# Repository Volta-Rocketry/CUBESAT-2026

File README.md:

# CUBESAT-2026
Repo for the CUBESAT - 2026

/ IMAGE OR VIDEO

## Description

Here goes the project description

## Features
Here goes the features and capabilities

## Requirements and Software
Here goes the requirements for developers to run the code

## Usage
Here goes a little guide or referral to usage manual

### IMPORTANT
Here goes important notes

## Authors and Acknowledgments
Here goes the authors and acknowledgments

## License
Here goes the license information

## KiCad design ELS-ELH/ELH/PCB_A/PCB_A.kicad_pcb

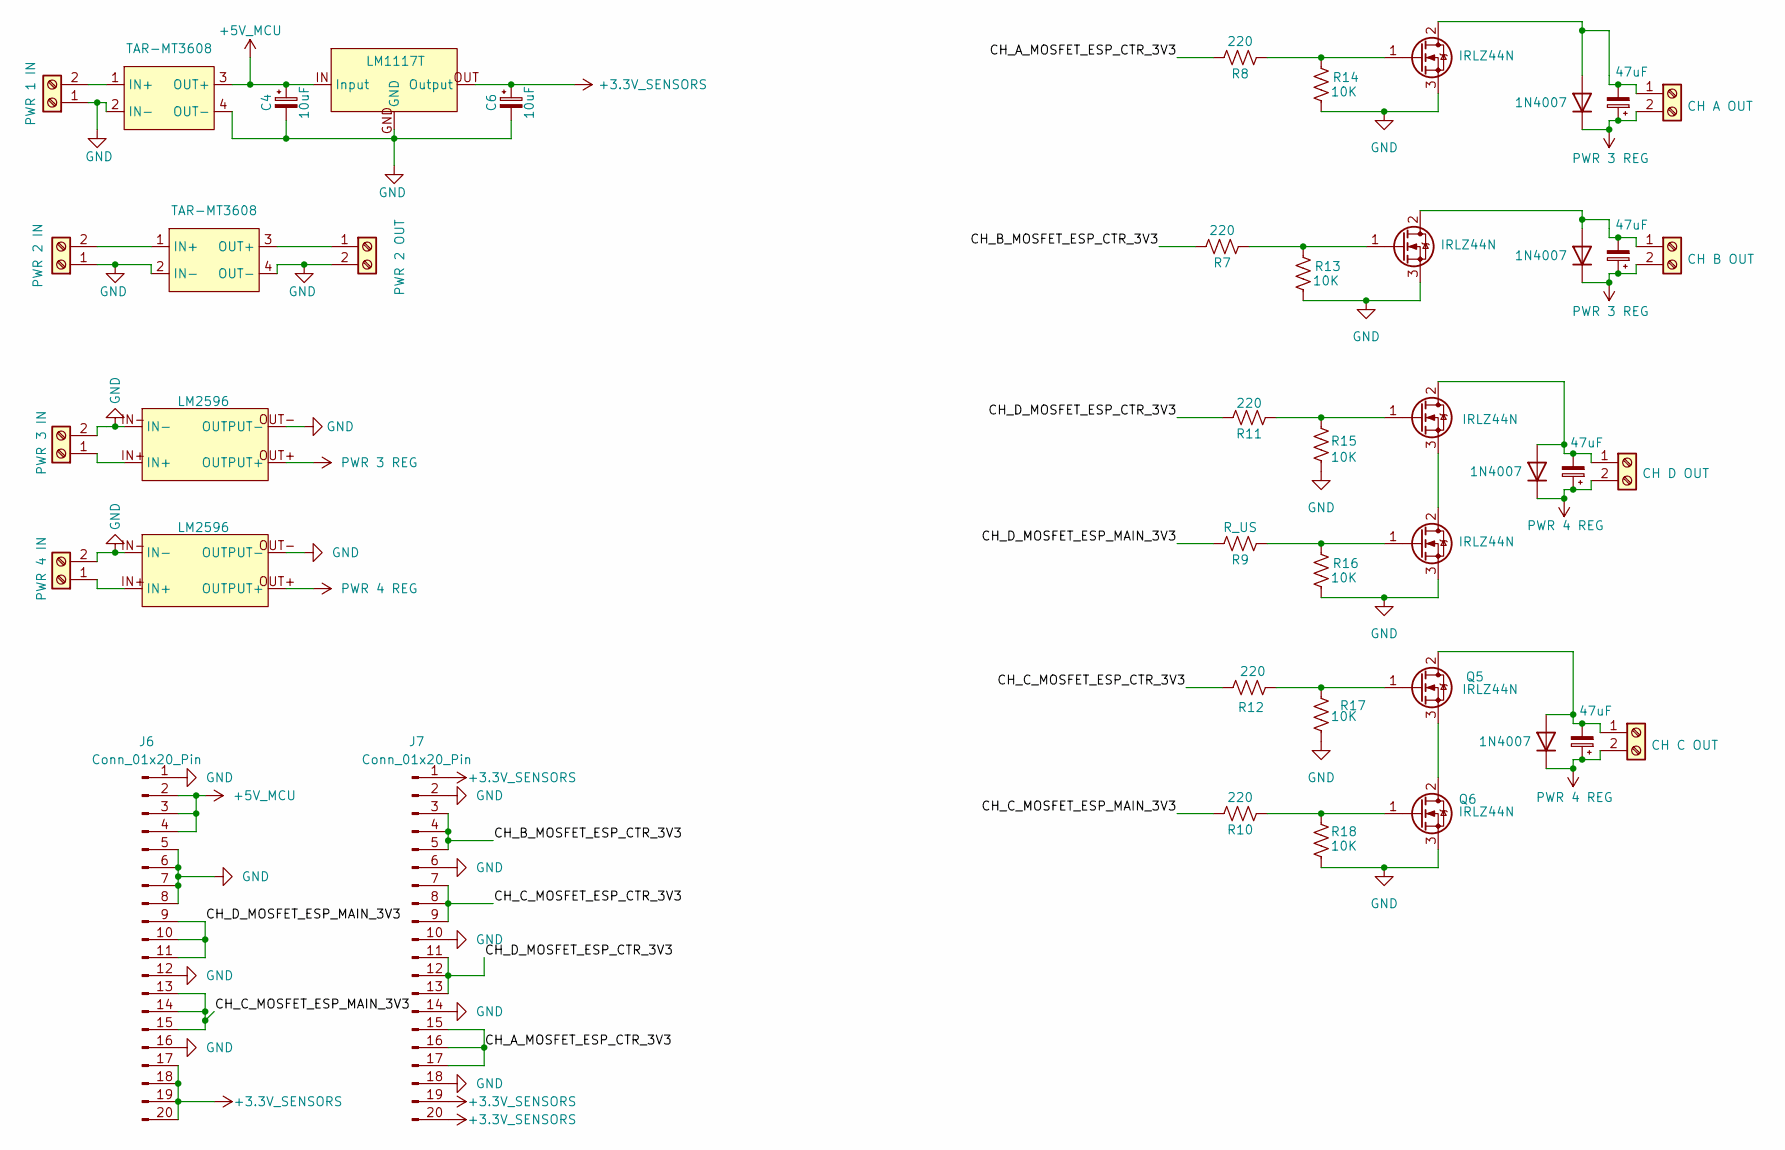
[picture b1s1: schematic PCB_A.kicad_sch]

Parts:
BOOST1, BOOST2: TAR-MT3608
C4, C6: 10uF; CP_Radial_D5.0mm_P2.00mm
C7, C8, C9, C10: 47uF; CP_Radial_D6.3mm_P2.50mm
D2, D3, D4, D5: 1N4007; D_DO-41_SOD81_P10.16mm_Horizontal
J1: PWR 1 IN; Bornera 2P
J2: PWR 2 IN; Bornera 2P
J3: PWR 3 IN; Bornera 2P
J4: PWR 4 IN; Bornera 2P
J5: PWR 2 OUT; Bornera 2P
J6, J7: Conn_01x20_Pin; PinHeader_1x20_P2.54mm_Vertical
J9: CH D OUT; Bornera 2P
J10: CH C OUT; Bornera 2P
J11: CH A OUT; Bornera 2P
J12: CH B OUT; Bornera 2P
Q1, Q2, Q3, Q4, Q5, Q6: IRLZ44N; TO-220-3_Vertical
R7, R8, R10, R11, R12: 220; R_Axial_DIN0207_L6.3mm_D2.5mm_P7.62mm_Horizontal
R9: R_US; R_Axial_DIN0207_L6.3mm_D2.5mm_P7.62mm_Horizontal
R13, R14, R15, R16, R17, R18: 10K; R_Axial_DIN0207_L6.3mm_D2.5mm_P7.62mm_Horizontal
Regulator1, Regulator2: LM2596
Regulator3: LM1117T

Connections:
+3.3V_SENSORS: C6.1, J6.17, J6.18, J6.19, J6.20, J7.1, J7.19, J7.20, Regulator3.OUT (Output)
+5V_MCU: BOOST1.3 (OUT+), C4.1, J6.2, J6.3, J6.4, Regulator3.IN (Input)
/CH_A_MOSFET_ESP_CTR_3V3: J7.15, J7.16, J7.17, R8.1
/CH_B_MOSFET_ESP_CTR_3V3: J7.3, J7.4, J7.5, R7.1
/CH_C_MOSFET_ESP_CTR_3V3: J7.7, J7.8, J7.9, R12.1
/CH_C_MOSFET_ESP_MAIN_3V3: J6.13, J6.14, J6.15, R10.1
/CH_D_MOSFET_ESP_CTR_3V3: J7.11, J7.12, J7.13, R11.1
/CH_D_MOSFET_ESP_MAIN_3V3: J6.9, J6.10, J6.11, R9.1
GND: BOOST1.2 (IN-), BOOST1.4 (OUT-), BOOST2.2 (IN-), BOOST2.4 (OUT-), C4.2, C6.2, J1.1, J2.1, J3.2, J4.2, J5.2, J6.1, J6.5, J6.6, J6.7, J6.8, J6.12, J6.16, J7.2, J7.6, J7.10, J7.14, J7.18, Q1.3 (S), Q2.3 (S), Q4.3 (S), Q6.3 (S), R13.2, R14.2, R15.2, R16.2, R17.2, R18.2, Regulator1.IN-, Regulator1.OUT- (OUTPUT-), Regulator2.IN-, Regulator2.OUT- (OUTPUT-), Regulator3.GND
unnamed: BOOST1.1 (IN+), J1.2
unnamed: BOOST2.1 (IN+), J2.2
unnamed: BOOST2.3 (OUT+), J5.1
unnamed: C7.2, D2.2 (A), J9.1, Q3.2 (D)
unnamed: C8.2, D3.2 (A), J10.1, Q5.2 (D)
unnamed: C9.2, D4.2 (A), J11.1, Q2.2 (D)
unnamed: C10.2, D5.2 (A), J12.1, Q1.2 (D)
unnamed: J3.1, Regulator1.IN+
unnamed: J4.1, Regulator2.IN+
unnamed: Q1.1 (G), R7.2, R13.1
unnamed: Q2.1 (G), R8.2, R14.1
unnamed: Q3.1 (G), R11.2, R15.1
unnamed: Q3.3 (S), Q4.2 (D)
unnamed: Q4.1 (G), R9.2, R16.1
unnamed: Q5.1 (G), R12.2, R17.1
unnamed: Q5.3 (S), Q6.2 (D)
unnamed: Q6.1 (G), R10.2, R18.1
PWR 3 REG: C9.1, C10.1, D4.1 (K), D5.1 (K), J11.2, J12.2, Regulator1.OUT+ (OUTPUT+)
PWR 4 REG: C7.1, C8.1, D2.1 (K), D3.1 (K), J9.2, J10.2, Regulator2.OUT+ (OUTPUT+)

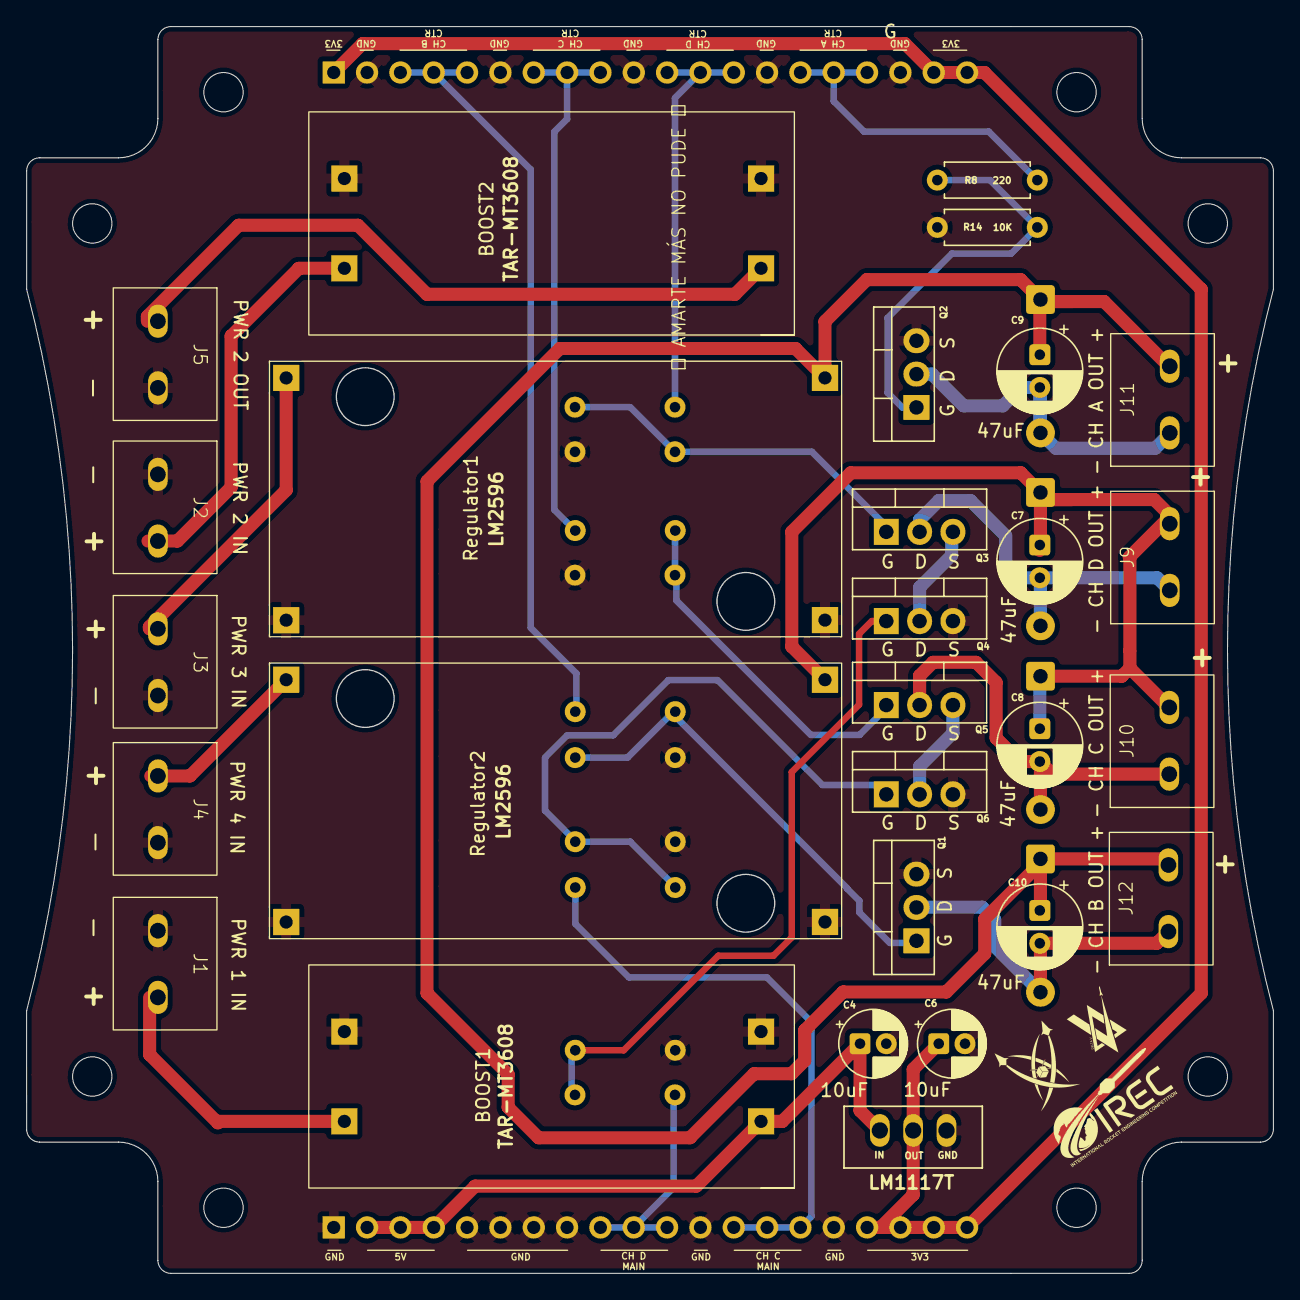
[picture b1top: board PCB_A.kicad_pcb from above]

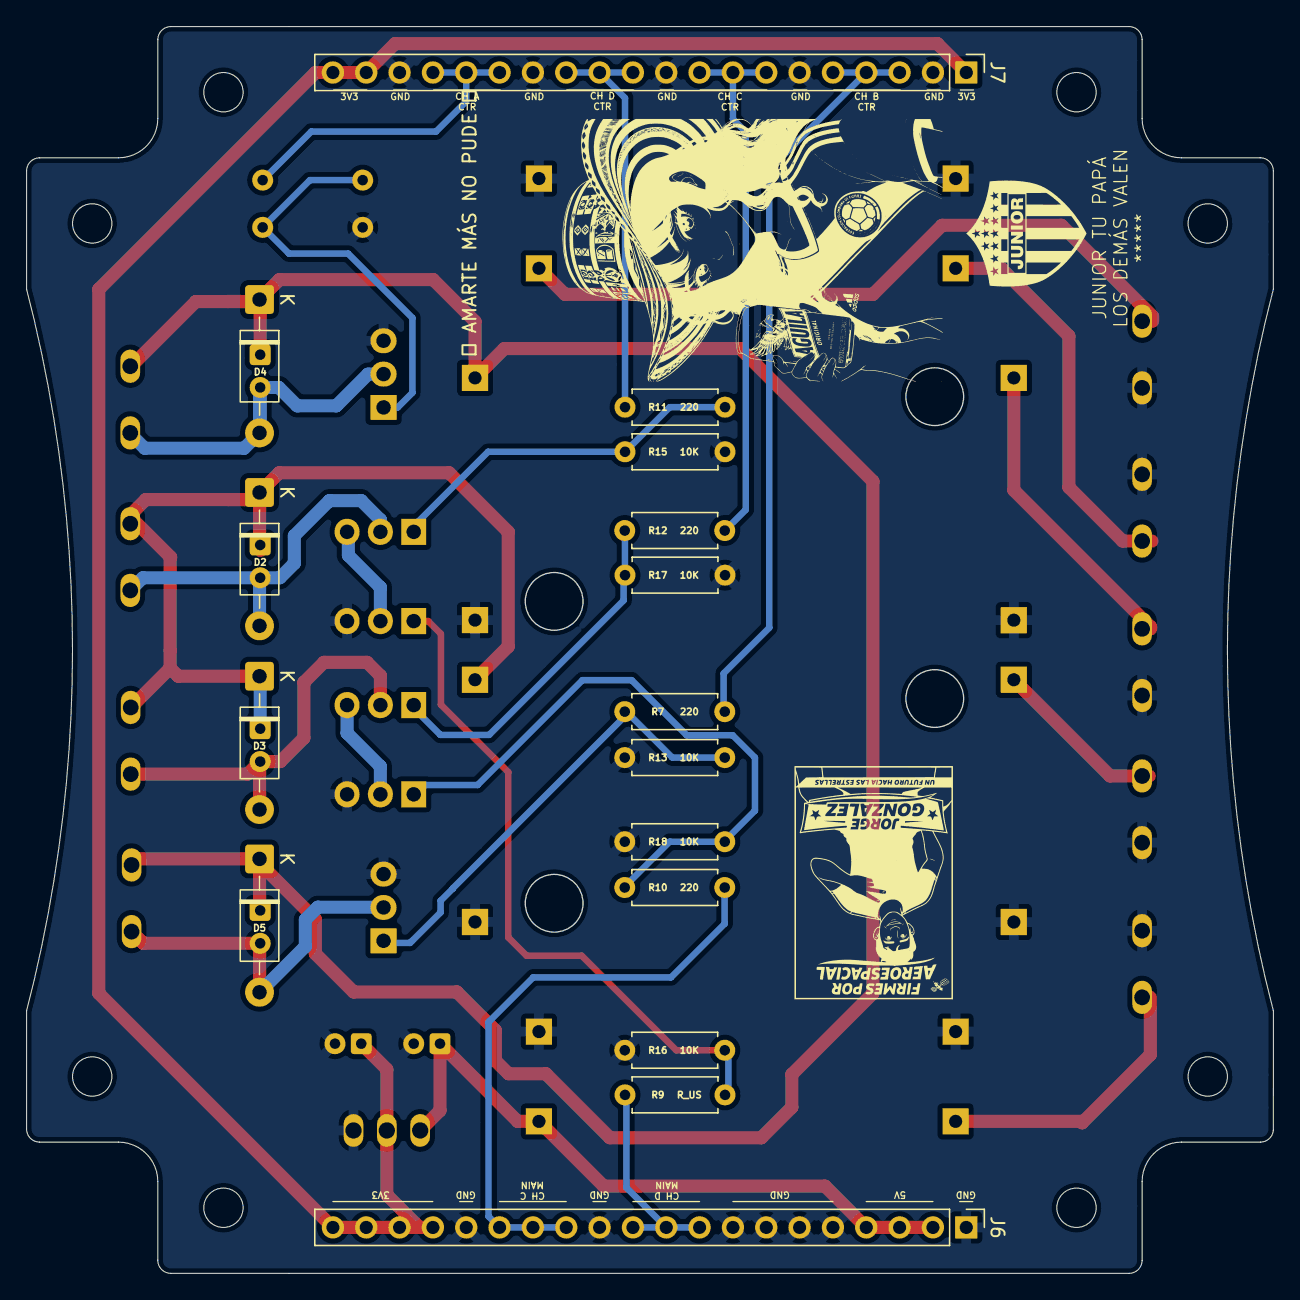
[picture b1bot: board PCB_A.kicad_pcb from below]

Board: 2 copper layers, 95.0 x 95.0 mm, 44 parts (16 on the bottom side), 28 nets.

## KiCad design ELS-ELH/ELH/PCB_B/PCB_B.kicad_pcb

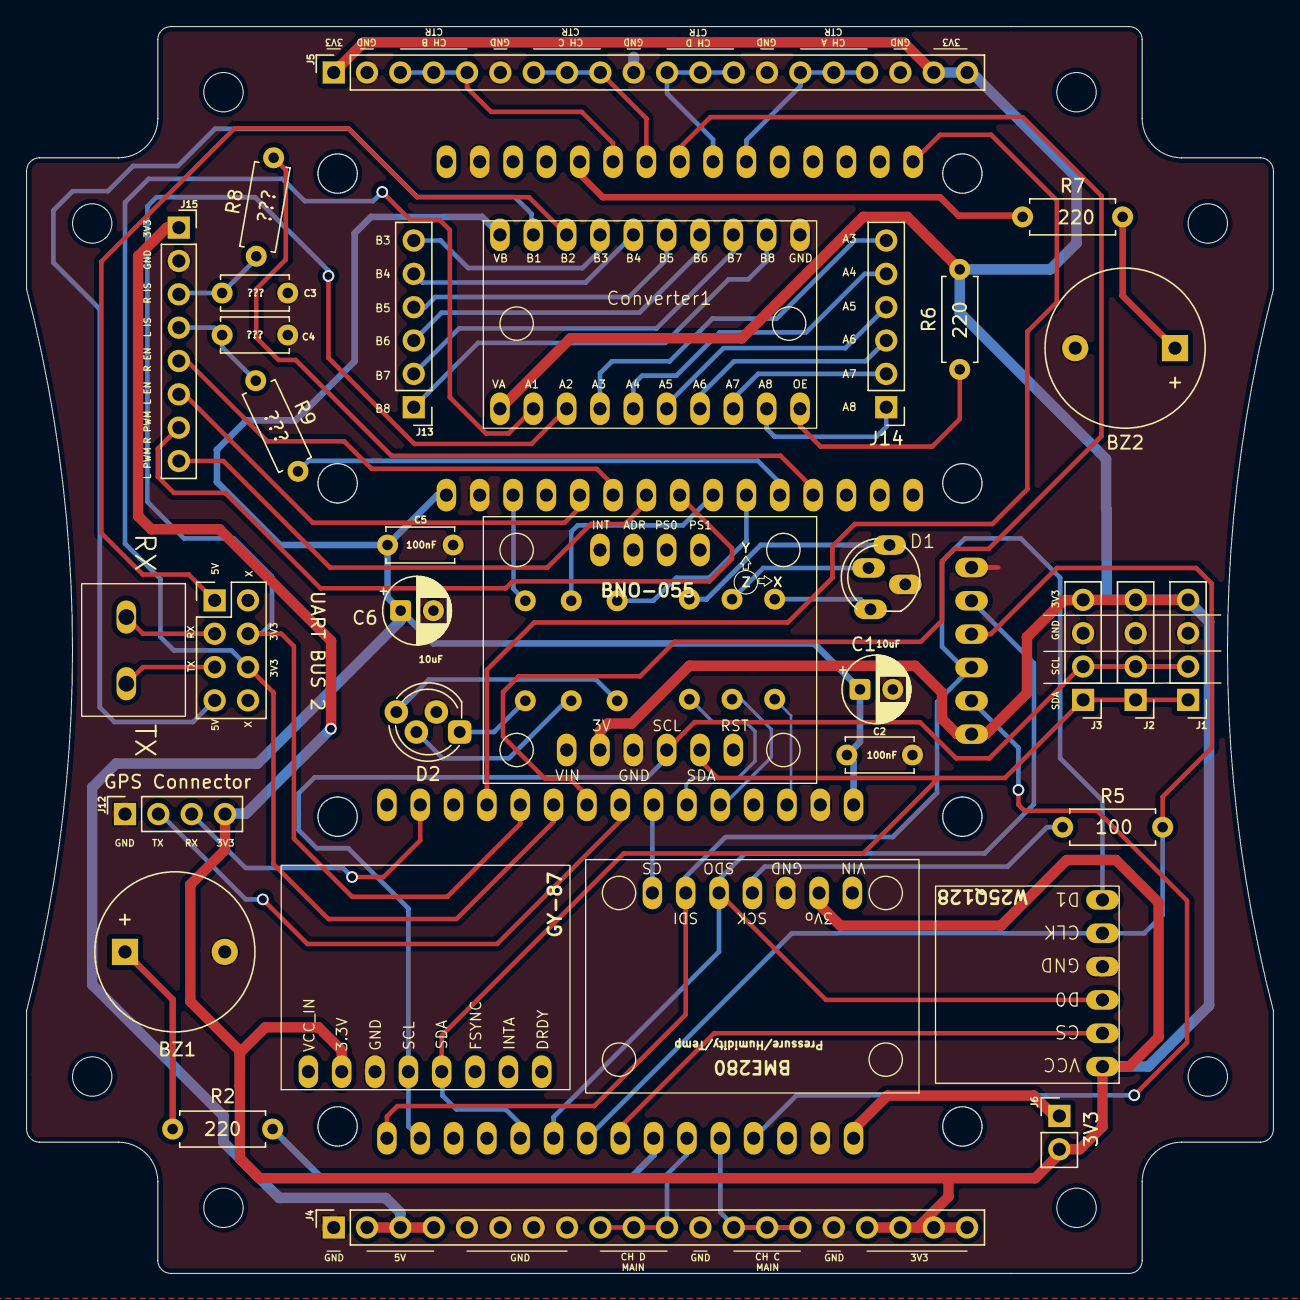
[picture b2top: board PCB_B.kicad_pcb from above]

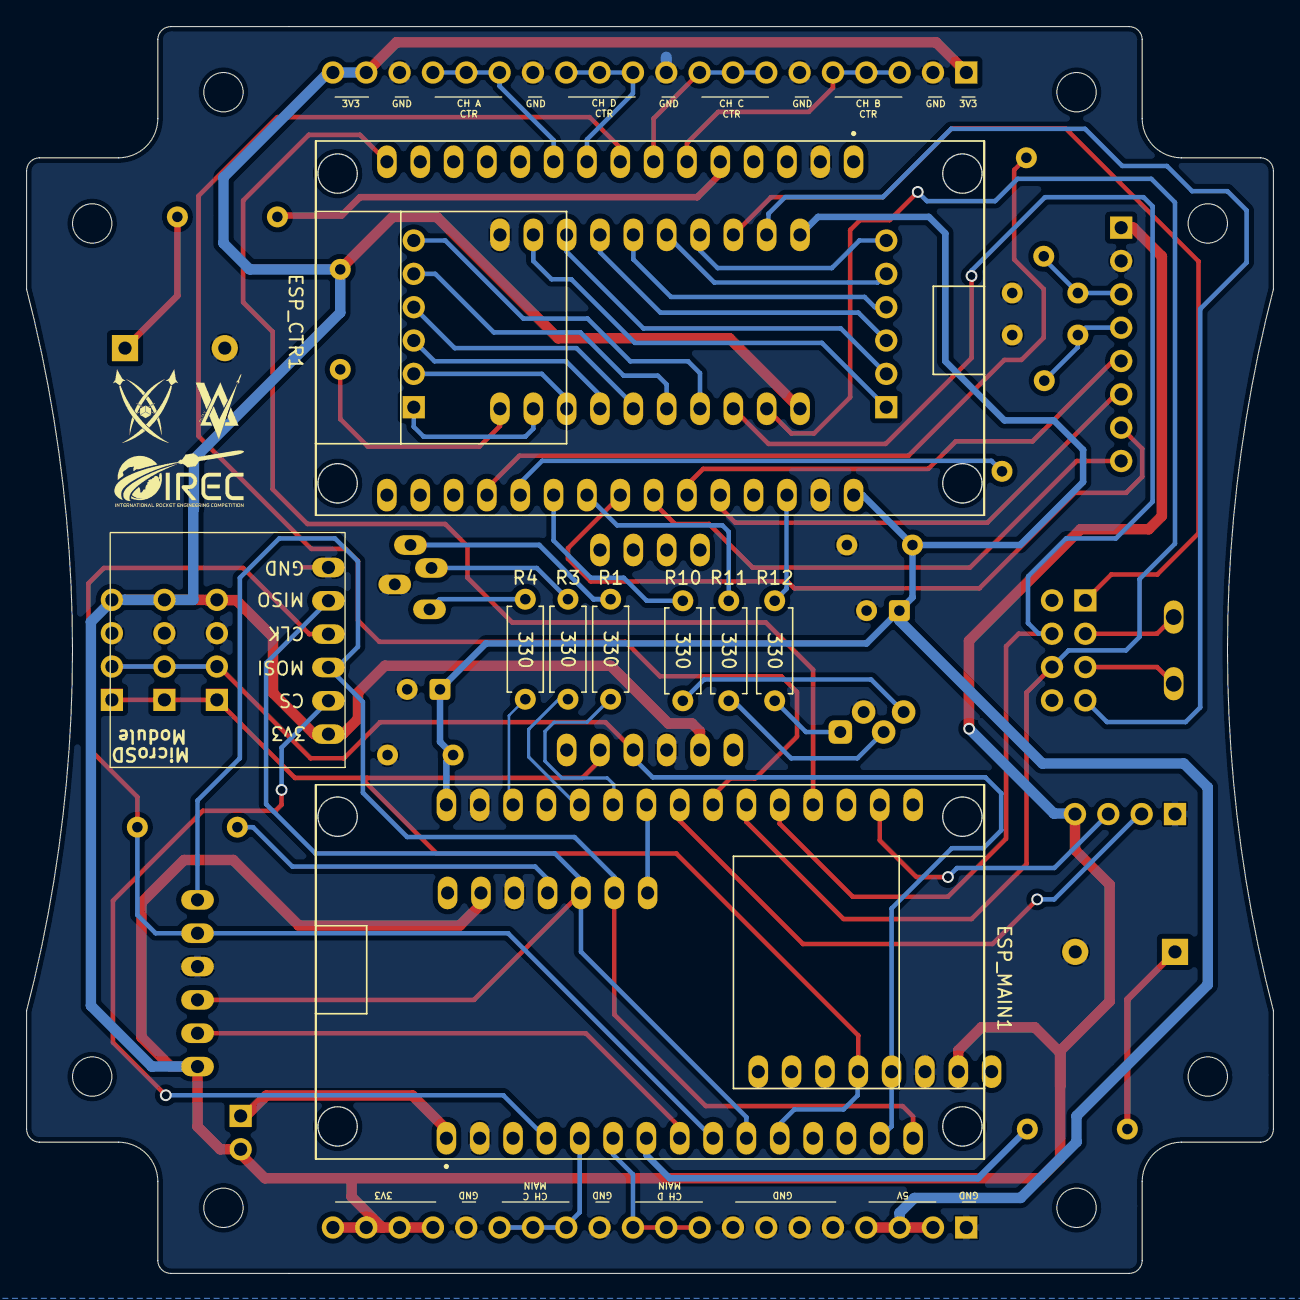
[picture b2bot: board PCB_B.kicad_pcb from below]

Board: 2 copper layers, 95.0 x 95.0 mm, 42 parts (9 on the bottom side), 66 nets.

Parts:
BME1: BME280
BZ1, BZ2: Buzzer; Buzzer_12x9.5RM7.6
Bornera1: UART BUS 2; Bornera 2P
C1, C6: 10uF; CP_Radial_D5.0mm_P2.50mm
C2, C5: 100nF; C_Disc_D5.0mm_W2.5mm_P5.00mm
C3, C4: ???; C_Disc_D5.0mm_W2.5mm_P5.00mm
Converter1: TXS0108E
D1: LED_RKGB; LED RGB
D2: LED_RKGB; LED_D5.0mm-4_RGB_Staggered_Pins
ESP_CTR1: ESP32 DEVKIT V1
ESP_MAIN1: ESP32 DEVKIT V1
IMU1: BNO055
J1: I2C Bus Connector 1; PinHeader_1x04_P2.54mm_Vertical
J2: I2C Bus Connector 2; PinHeader_1x04_P2.54mm_Vertical
J3: I2C Bus Connector 3; PinHeader_1x04_P2.54mm_Vertical
J4, J5: Conn_01x20_Pin; PinSocket_1x20_P2.54mm_Vertical
J6: Conn_01x02_Pin; PinHeader_1x02_P2.54mm_Vertical
J12: GPS Connector; PinSocket_1x04_P2.54mm_Vertical
J13, J14: Conn_01x06_Pin; PinHeader_1x06_P2.54mm_Vertical
J15: Conn_01x08_Pin; PinSocket_1x08_P2.54mm_Vertical
J16: Conn_02x04_Odd_Even; PinHeader_2x04_P2.54mm_Vertical
R1, R3, R4, R10, R11, R12: 330; R_Axial_DIN0207_L6.3mm_D2.5mm_P7.62mm_Horizontal
R2, R6, R7: 220; R_Axial_DIN0207_L6.3mm_D2.5mm_P7.62mm_Horizontal
R5: 100; R_Axial_DIN0207_L6.3mm_D2.5mm_P7.62mm_Horizontal
R8, R9: ???; R_Axial_DIN0207_L6.3mm_D2.5mm_P7.62mm_Horizontal
SD_Adapter1: Micro SD Module; MicroSD Module
U1: GY-87
W25QXX1: W25Q128

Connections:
+3.3V_ESP_MAIN: ESP_MAIN1.3V3, J6.1
+3.3V_SENSORS: BME1.3Vo (3V0), Converter1.11 (VA), IMU1.3V, J1.4, J2.4, J3.4, J4.17, J4.18, J4.19, J4.20, J5.1, J5.19, J5.20, J6.2, J12.4, J15.1, R6.1, SD_Adapter1.1 (3V3), U1.2 (3.3V), W25QXX1.1 (VCC)
+5V_MCU: C1.1, C2.2, C5.2, C6.1, Converter1.1 (VB), ESP_CTR1.VIN, ESP_MAIN1.VIN, J4.2, J4.3, J4.4
/BUZZER_SIGNAL_ESP_CTR_3V3: ESP_CTR1.D4, R7.1
/BUZZER_SIGNAL_ESP_MAIN_3V3: ESP_MAIN1.TX2 (D17/TX2), R2.1
/CH_A_MOSFET_ESP_CTR_3V3: ESP_CTR1.D19, J5.15, J5.16, J5.17
/CH_B_MOSFET_ESP_CTR_3V3: ESP_CTR1.RX2 (D16/RX2), J5.3, J5.4, J5.5
/CH_C_MOSFET_ESP_CTR_3V3: ESP_CTR1.TX2 (D17/TX2), J5.7, J5.8, J5.9
/CH_C_MOSFET_ESP_MAIN_3V3: ESP_MAIN1.D4, J4.13, J4.14, J4.15
/CH_D_MOSFET_ESP_CTR_3V3: ESP_CTR1.D18, J5.11, J5.12, J5.13
/CH_D_MOSFET_ESP_MAIN_3V3: ESP_MAIN1.RX2 (D16/RX2), J4.9, J4.10, J4.11
/CS_BME_ESP_MAIN_3V3: BME1.CS, ESP_MAIN1.D26
/CS_FLASH_ESP_MAIN_3V3: ESP_MAIN1.D5, W25QXX1.2 (CS)
/CS_SD_ESP_MAIN_3V3: ESP_MAIN1.D2, SD_Adapter1.2 (CS)
/LED_BLUE_SIGNAL_ESP_CTR_3V3: ESP_CTR1.D32, R10.2
/LED_BLUE_SIGNAL_ESP_MAIN_3V3: ESP_MAIN1.D27, R1.2
/LED_GREEN_SIGNAL_ESP_CTR_3V3: ESP_CTR1.D33, R11.2
/LED_GREEN_SIGNAL_ESP_MAIN_3V3: ESP_MAIN1.D14, R3.2
/LED_RED_SIGNAL_ESP_CTR_3V3: ESP_CTR1.D13, R12.2
/LED_RED_SIGNAL_ESP_MAIN_3V3: ESP_MAIN1.D13, R4.2
/LPWM_BTS7960_ESP_CTR_3V3: ESP_CTR1.D26, J15.8
/L_EN_BTS7960_ESP_CTR_3V3: ESP_CTR1.D14, J15.6
/L_IS_BTS7960_ESP_CTR_3V3: C4.1, J15.4, R9.1
/MISO_SPI_BUS1_ESP_MAIN_3V3: BME1.SD0, ESP_MAIN1.D19, SD_Adapter1.5 (MISO), W25QXX1.3 (DO)
/MOSI_SPI_BUS1_ESP_MAIN_3V3: BME1.SDI, ESP_MAIN1.D23, SD_Adapter1.3 (MOSI), W25QXX1.6 (DI)
/RPWM_BTS7960_ESP_CTR_3V3: ESP_CTR1.D25, J15.7
/RX_UART_BUS1_ESP_MAIN_3V3: ESP_CTR1.D23, ESP_MAIN1.D34
/RX_UART_BUS2_5V: Converter1.3 (B2), J16.1
/RX_UART_BUS2_ESP_MAIN_3V3: Converter1.13 (A2), ESP_MAIN1.D35, J16.4
/RX_UART_BUS3_ESP_MAIN_3V3: ESP_MAIN1.VP (36/VP), J12.3
/R_EN_BTS7960_ESP_CTR_3V3: ESP_CTR1.D27, J15.5
/R_IS_BTS7960_ESP_CTR_3V3: C3.2, J15.3, R8.1
/SCK_SPI_BUS1_ESP_MAIN_3V3: ESP_MAIN1.D18, R5.1, SD_Adapter1.4 (CLK), W25QXX1.5 (CLK)
/SCL_I2C_BUS1_ESP_MAIN_3V3: ESP_MAIN1.D22, IMU1.SCL (SCL/RX), J1.2, J2.2, J3.2, U1.4 (SCL)
/SDA_I2C_BUS1_ESP_MAIN_3V3: ESP_MAIN1.D21, IMU1.SDA (SDA/TX), J1.1, J2.1, J3.1, U1.5 (SDA)
/TX_UART_BUS1_ESP_MAIN_3V3: ESP_CTR1.D5, ESP_MAIN1.D33
/TX_UART_BUS2_5V: Converter1.2 (B1), J16.7
/TX_UART_BUS2_ESP_MAIN_3V3: Converter1.12 (A1), ESP_MAIN1.D32, J16.6
/TX_UART_BUS3_ESP_MAIN_3V3: ESP_MAIN1.D25, J12.2
GND: BME1.GND, BZ1.2 (-), BZ2.2 (-), C1.2, C2.1, C3.1, C4.2, C5.1, C6.2, Converter1.10 (GND), D1.2 (K), D2.2 (K), ESP_CTR1.GND, ESP_MAIN1.GND, IMU1.GND, J1.3, J2.3, J3.3, J4.1, J4.5, J4.6, J4.7, J4.8, J4.12, J4.16, J5.2, J5.6, J5.10, J5.14, J5.18, J12.1, J15.2, SD_Adapter1.6 (GND), U1.3 (GND), W25QXX1.4 (GND)
unnamed: BME1.SCK, R5.2
unnamed: BZ1.1 (+), R2.2
unnamed: BZ2.1 (+), R7.2
unnamed: Bornera1.1, J16.3
unnamed: Bornera1.2, J16.5
unnamed: Converter1.14 (A3), J14.6
unnamed: Converter1.15 (A4), J14.5
unnamed: Converter1.16 (A5), J14.4
unnamed: Converter1.17 (A6), J14.3
unnamed: Converter1.18 (A7), J14.2
unnamed: Converter1.19 (A8), J14.1
unnamed: Converter1.4 (B3), J13.6
unnamed: Converter1.5 (B4), J13.5
unnamed: Converter1.6 (B5), J13.4
unnamed: Converter1.7 (B6), J13.3
unnamed: Converter1.8 (B7), J13.2
unnamed: Converter1.9 (B8), J13.1
unnamed: Converter1.20 (OE), R6.2
unnamed: D1.4 (BA), R1.1
unnamed: D1.3 (GA), R3.1
unnamed: D1.1 (RA), R4.1
unnamed: D2.4 (BA), R10.1
unnamed: D2.3 (GA), R11.1
unnamed: D2.1 (RA), R12.1
unnamed: ESP_CTR1.D34, R8.2
unnamed: ESP_CTR1.D35, R9.2

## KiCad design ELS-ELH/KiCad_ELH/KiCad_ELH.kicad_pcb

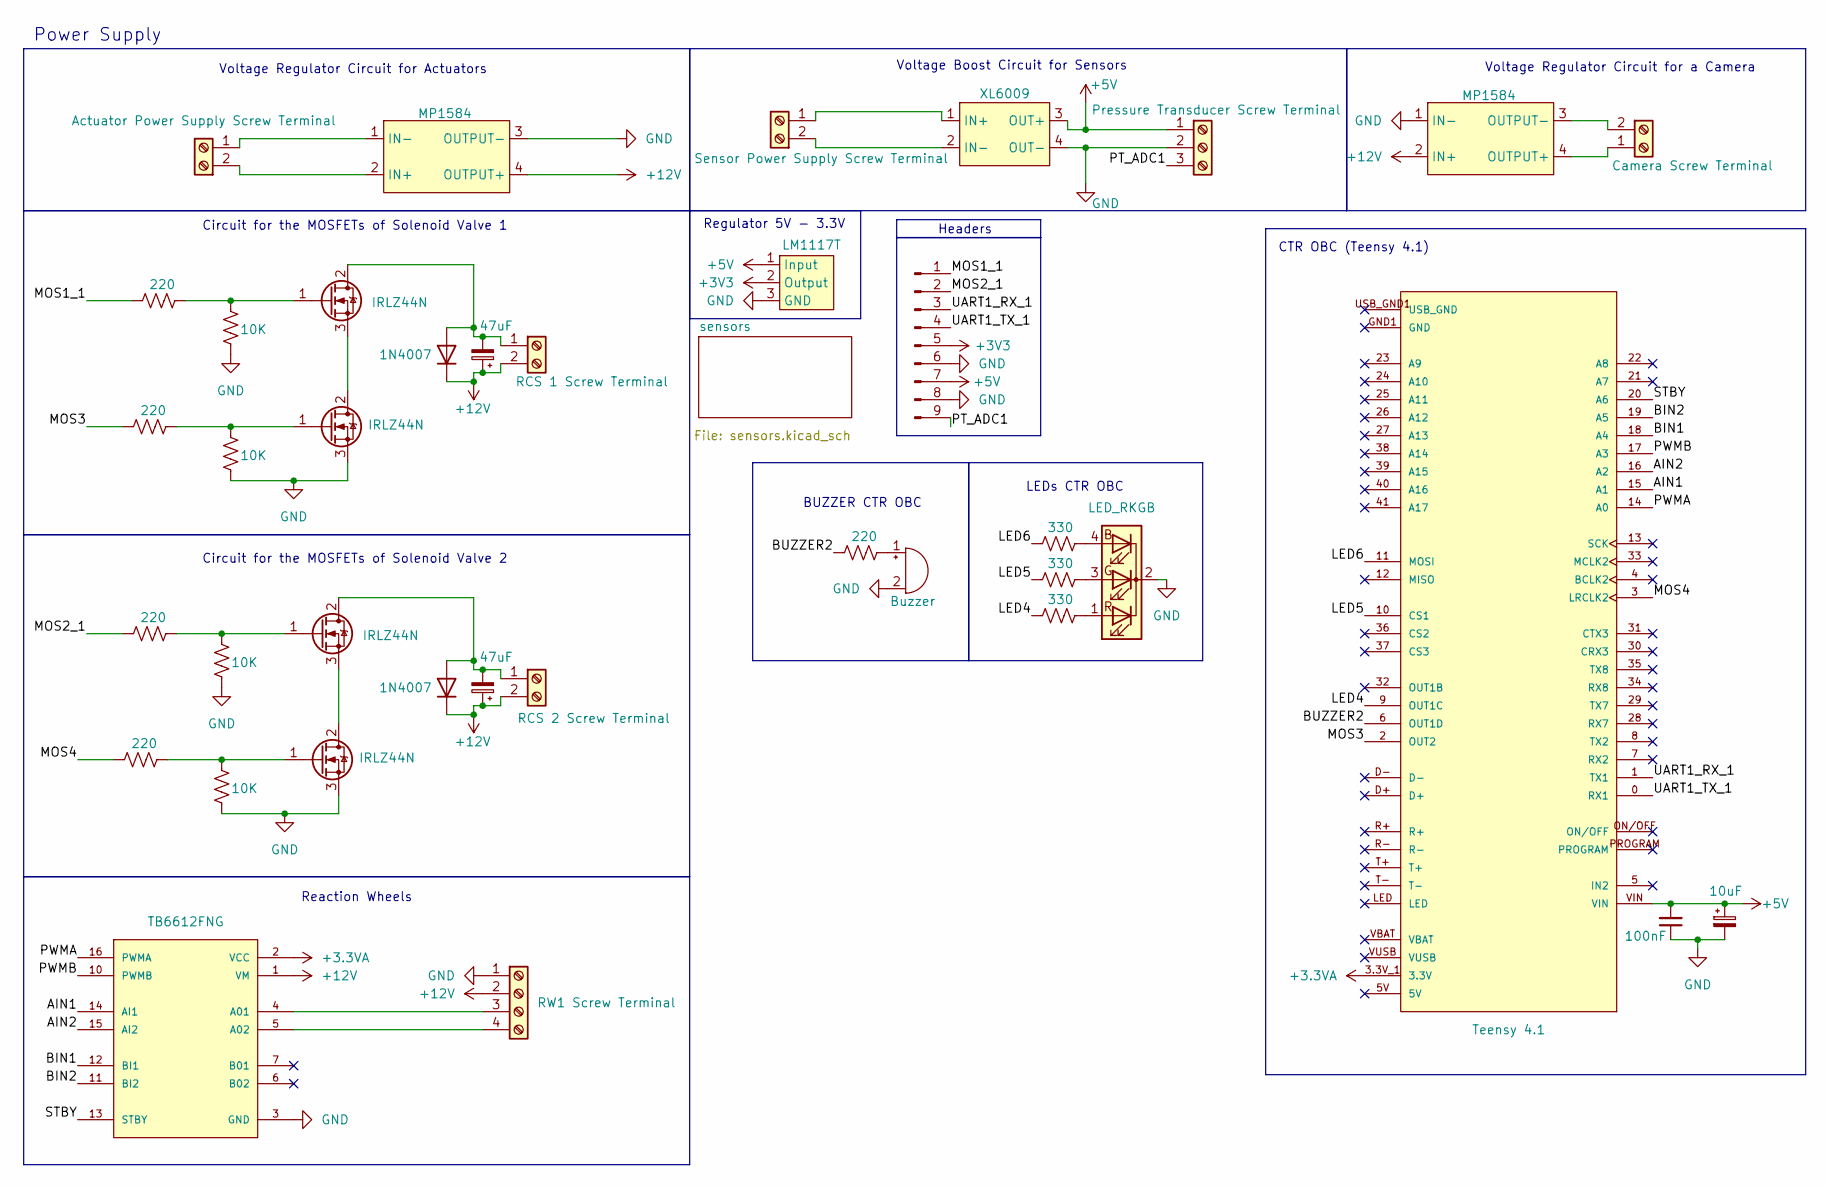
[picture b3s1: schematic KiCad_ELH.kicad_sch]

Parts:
BOOST1: XL6009; XL6009 Boost
BZ2: Buzzer; Buzzer_12x9.5RM7.6
Bornera2: Camera Screw Terminal; Bornera 2P
Bornera3: Actuator Power Supply Screw Terminal; Bornera 2P
Bornera4: RCS 2 Screw Terminal; Bornera 2P
Bornera5: RCS 1 Screw Terminal; Bornera 2P
Bornera6: Sensor Power Supply Screw Terminal; Bornera 2P
C1: 100nF; C_Disc_D5.0mm_W2.5mm_P5.00mm
C3: 10uF; CP_Radial_D5.0mm_P2.50mm
C9, C10: 47uF; CP_Radial_D6.3mm_P2.50mm
D1, D9: 1N4007; D_DO-41_SOD81_P10.16mm_Horizontal
D3: LED_RKGB; LED_D5.0mm-4_RGB_Staggered_Pins
Driver_DC2: TB6612FNG
J1: Pressure Transducer Screw Terminal; TerminalBlock_MaiXu_MX126-5.0-03P_1x03_P5.00mm
J2: Conn_01x09_Pin; Hirose_DF13-09P-1.25DSA_1x09_P1.25mm_Vertical
J8: RW1 Screw Terminal; TerminalBlock_MaiXu_MX126-5.0-04P_1x04_P5.00mm
Q1, Q2, Q4, Q6: IRLZ44N; TO-220-3_Vertical
R1, R2, R8: 330; R_Axial_DIN0207_L6.3mm_D2.5mm_P7.62mm_Horizontal
R3, R6, R9, R16, R20: 220; R_Axial_DIN0207_L6.3mm_D2.5mm_P7.62mm_Horizontal
R10, R11, R18, R19: 10K; R_Axial_DIN0207_L6.3mm_D2.5mm_P7.62mm_Horizontal
Regulator1: LM1117T
Regulator3, Regulator4: MP1584
Teensy3: Teensy 4.1

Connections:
+3.3VA: Driver_DC2.2 (VCC), Teensy3.3.3V_1 (3.3V), Teensy3.3.3V_2 (3.3V), Teensy3.3.3V_3 (3.3V)
+3V3: J2.5, Regulator1.2 (Output)
+5V: BOOST1.3 (OUT+), C1.2, C3.1, J1.1, J2.7, Regulator1.1 (Input), Teensy3.VIN
+12V: Bornera4.2, Bornera5.2, C9.1, C10.1, D1.1 (K), D9.1 (K), Driver_DC2.1 (VM), J8.2, Regulator3.2 (IN+), Regulator4.4 (OUTPUT+)
/AIN1: Driver_DC2.14 (AI1), Teensy3.15 (A1)
/AIN2: Driver_DC2.15 (AI2), Teensy3.16 (A2)
/BIN1: Driver_DC2.12 (BI1), Teensy3.18 (A4)
/BIN2: Driver_DC2.11 (BI2), Teensy3.19 (A5)
/BUZZER2: R9.1, Teensy3.6 (OUT1D)
/LED4: R8.2, Teensy3.9 (OUT1C)
/LED5: R2.2, Teensy3.10 (CS1)
/LED6: R1.2, Teensy3.11 (MOSI)
/MOS1_1: J2.1, R16.1
/MOS2_1: J2.2, R6.1
/MOS3: R20.1, Teensy3.2 (OUT2)
/MOS4: R3.1, Teensy3.3 (LRCLK2)
/PT_ADC1: J1.3, J2.9
/PWMA: Driver_DC2.16 (PWMA), Teensy3.14 (A0)
/PWMB: Driver_DC2.10 (PWMB), Teensy3.17 (A3)
/STBY: Driver_DC2.13 (STBY), Teensy3.20 (A6)
/UART1_RX_1: J2.3, Teensy3.1 (TX1)
/UART1_TX_1: J2.4, Teensy3.0 (RX1)
unnamed: BOOST1.1 (IN+), Bornera6.1 (Pin_2)
unnamed: BOOST1.2 (IN-), Bornera6.2 (Pin_1)
unnamed: BZ2.1 (+), R9.2
unnamed: Bornera2.2 (Pin_1), Regulator3.3 (OUTPUT-)
unnamed: Bornera2.1 (Pin_2), Regulator3.4 (OUTPUT+)
unnamed: Bornera3.2 (Pin_1), Regulator4.2 (IN+)
unnamed: Bornera3.1 (Pin_2), Regulator4.1 (IN-)
unnamed: Bornera4.1, C10.2, D1.2 (A), Q1.2 (D)
unnamed: Bornera5.1, C9.2, D9.2 (A), Q6.2 (D)
unnamed: D3.4 (BA), R1.1
unnamed: D3.3 (GA), R2.1
unnamed: D3.1 (RA), R8.1
unnamed: Driver_DC2.4 (A01), J8.3
unnamed: Driver_DC2.5 (A02), J8.4
unnamed: Q1.1 (G), R6.2, R10.1
unnamed: Q1.3 (S), Q4.2 (D)
unnamed: Q2.2 (D), Q6.3 (S)
unnamed: Q2.1 (G), R19.1, R20.2
unnamed: Q4.1 (G), R3.2, R11.1
unnamed: Q6.1 (G), R16.2, R18.1

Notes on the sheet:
Regulator 5V - 3.3V
Reaction Wheels
Circuit for the MOSFETs of Solenoid Valve 2
Power Supply
Voltage Regulator Circuit for a Camera
BUZZER CTR OBC
LEDs CTR OBC
Voltage Regulator Circuit for Actuators
Headers
Circuit for the MOSFETs of Solenoid Valve 1
CTR OBC (Teensy 4.1)
Voltage Boost Circuit for Sensors

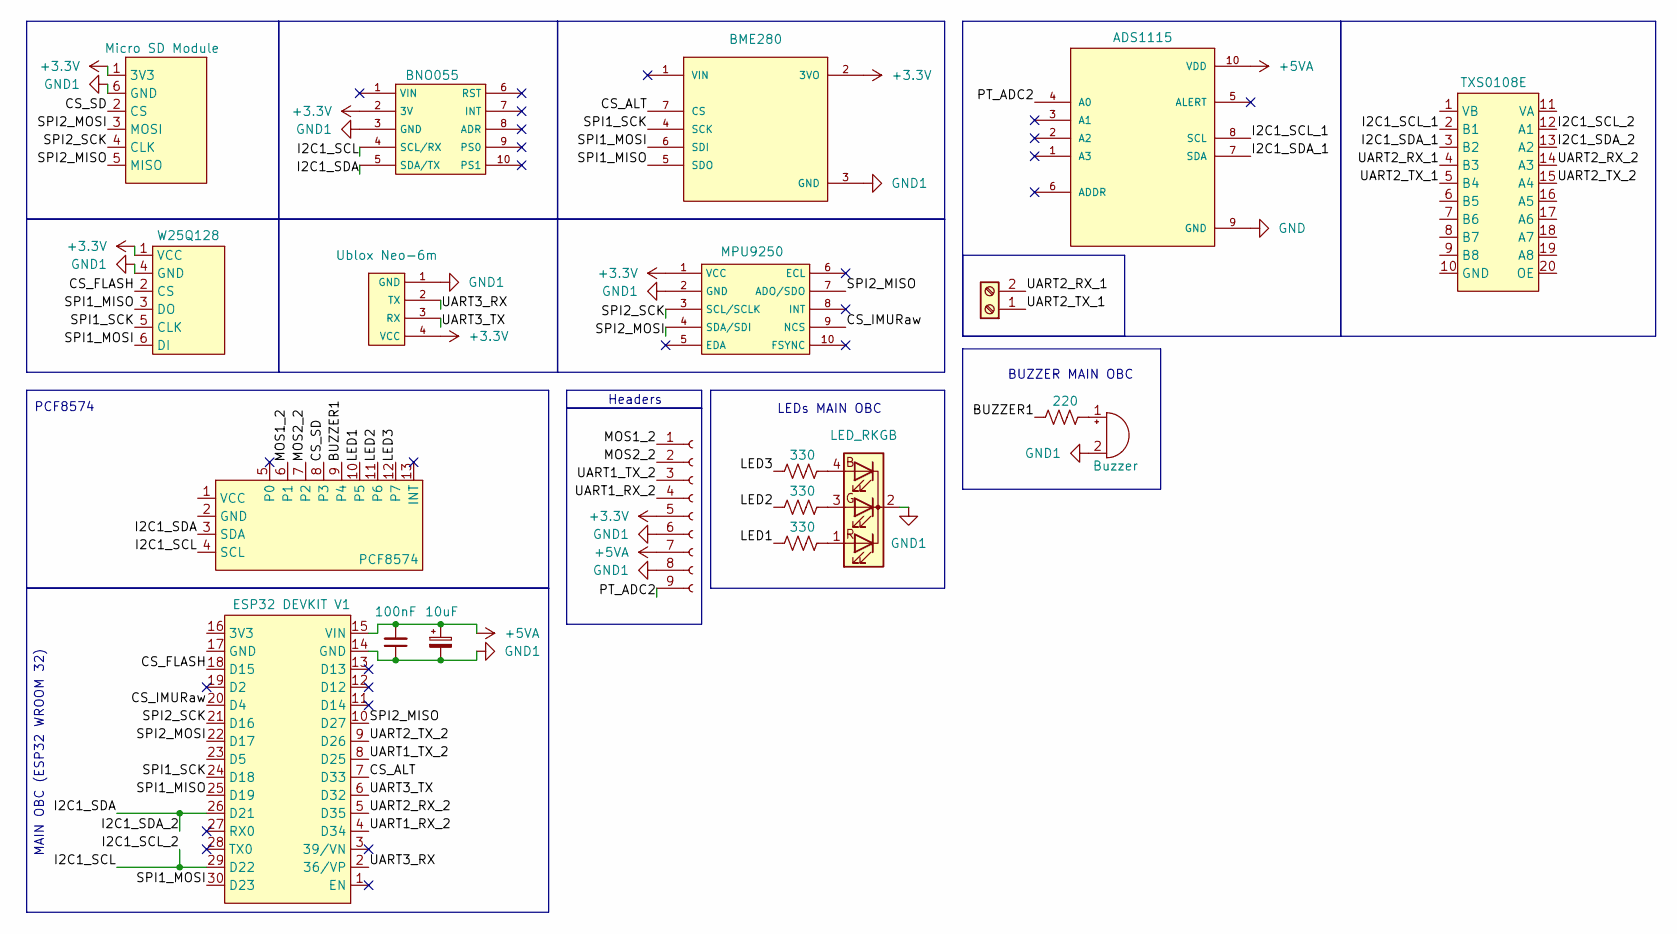
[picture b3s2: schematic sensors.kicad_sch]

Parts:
ADC1: ADS1115
Adapter1: PCF8574
BME2: BME280
BZ1: Buzzer; Buzzer_12x9.5RM7.6
Bornera7: COM Camera Screw Terminal; Bornera 2P
C2: 100nF; C_Disc_D5.0mm_W2.5mm_P5.00mm
C13: 10uF; CP_Radial_D5.0mm_P2.50mm
Converter1: TXS0108E
D10: LED_RKGB; LED_D5.0mm-4_RGB_Staggered_Pins
ESP1: ESP32 DEVKIT V1
GPS1: Ublox Neo-6m
IMU1: MPU9250
IMU3: BNO055
J11: Conn_01x09_Socket; Hirose_DF13-09P-1.25DSA_1x09_P1.25mm_Vertical
R4, R5, R7: 330; R_Axial_DIN0207_L6.3mm_D2.5mm_P7.62mm_Horizontal
R12: 220; R_Axial_DIN0207_L6.3mm_D2.5mm_P7.62mm_Horizontal
SD_Adapter1: Micro SD Module; MicroSD Module
W25QXX1: W25Q128

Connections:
+3.3V: BME2.2 (3VO), Converter1.11 (VA), Converter1.20 (OE), GPS1.4 (VCC), IMU1.1 (VCC), IMU3.2 (3V), J11.5, SD_Adapter1.1 (3V3), W25QXX1.1 (VCC)
+5VA: ADC1.10 (VDD), Adapter1.1 (VCC), C2.2, C13.1, Converter1.1 (VB), ESP1.15 (VIN), J11.7
/sensors/BUZZER1: Adapter1.9 (P4), R12.1
/sensors/CS_ALT: BME2.7 (CS), ESP1.7 (D33)
/sensors/CS_FLASH: ESP1.18 (D15), W25QXX1.2 (CS)
/sensors/CS_IMURaw: ESP1.20 (D4), IMU1.9 (NCS)
/sensors/CS_SD: Adapter1.8 (P3), SD_Adapter1.2 (CS)
/sensors/I2C1_SCL: Adapter1.4 (SCL), Converter1.12 (A1), ESP1.29 (D22), IMU3.4 (SCL/RX)
/sensors/I2C1_SCL_1: ADC1.8 (SCL), Converter1.2 (B1)
/sensors/I2C1_SDA: Adapter1.3 (SDA), Converter1.13 (A2), ESP1.26 (D21), IMU3.5 (SDA/TX)
/sensors/I2C1_SDA_1: ADC1.7 (SDA), Converter1.3 (B2)
/sensors/LED1: Adapter1.10 (P5), R4.2
/sensors/LED2: Adapter1.11 (P6), R5.2
/sensors/LED3: Adapter1.12 (P7), R7.2
/sensors/MOS1_2: Adapter1.6 (P1), J11.1
/sensors/MOS2_2: Adapter1.7 (P2), J11.2
/sensors/PT_ADC2: ADC1.4 (A0), J11.9
/sensors/SPI1_MISO: BME2.5 (SDO), ESP1.25 (D19), W25QXX1.3 (DO)
/sensors/SPI1_MOSI: BME2.6 (SDI), ESP1.30 (D23), W25QXX1.6 (DI)
/sensors/SPI1_SCK: BME2.4 (SCK), ESP1.24 (D18), W25QXX1.5 (CLK)
/sensors/SPI2_MISO: ESP1.10 (D27), IMU1.7 (ADO/SDO), SD_Adapter1.5 (MISO)
/sensors/SPI2_MOSI: ESP1.22 (D17), IMU1.4 (SDA/SDI), SD_Adapter1.3 (MOSI)
/sensors/SPI2_SCK: ESP1.21 (D16), IMU1.3 (SCL/SCLK), SD_Adapter1.4 (CLK)
/sensors/UART1_RX_2: ESP1.4 (D34), J11.4
/sensors/UART1_TX_2: ESP1.8 (D25), J11.3
/sensors/UART2_RX_1: Bornera7.2, Converter1.4 (B3)
/sensors/UART2_RX_2: Converter1.14 (A3), ESP1.5 (D35)
/sensors/UART2_TX_1: Bornera7.1, Converter1.5 (B4)
/sensors/UART2_TX_2: Converter1.15 (A4), ESP1.9 (D26)
/sensors/UART3_RX: ESP1.2 (36/VP), GPS1.2 (TX)
/sensors/UART3_TX: ESP1.6 (D32), GPS1.3 (RX)
GND1: Adapter1.2 (GND), BME2.3 (GND), BZ1.2 (-), C2.1, C13.2, D10.2 (K), ESP1.14 (GND), GPS1.1 (GND), IMU1.2 (GND), IMU3.3 (GND), J11.6, J11.8, SD_Adapter1.6 (GND), W25QXX1.4 (GND)
unnamed: BZ1.1 (+), R12.2
unnamed: D10.4 (BA), R7.1
unnamed: D10.3 (GA), R5.1
unnamed: D10.1 (RA), R4.1

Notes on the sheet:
BUZZER MAIN OBC
Headers
LEDs MAIN OBC
MAIN OBC (ESP32 WROOM 32)
PCF8574

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
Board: 2 copper layers, 58 parts (2 on the bottom side), 79 nets, no tracks yet.

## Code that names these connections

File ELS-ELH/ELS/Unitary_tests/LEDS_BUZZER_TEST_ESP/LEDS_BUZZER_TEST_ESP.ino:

#define LED1 27  // R
#define LED2 14  // G
#define LED3 13  // B
#define BUZZER 17

void setup() {
  Serial.begin(115200);

  pinMode(LED1, OUTPUT);
  pinMode(LED2, OUTPUT);
  pinMode(LED3, OUTPUT);
  pinMode(BUZZER, OUTPUT);
}

// ---------------- PWM LED (software) ----------------
void pwmFade(int pin) {

  // subida
  for (int duty = 0; duty <= 255; duty++) {
    for (int i = 0; i < 255; i++) {
      digitalWrite(pin, (i < duty) ? HIGH : LOW);
      delayMicroseconds(30);
    }
    delay(2);
  }

  // bajada
  for (int duty = 255; duty >= 0; duty--) {
    for (int i = 0; i < 255; i++) {
      digitalWrite(pin, (i < duty) ? HIGH : LOW);
      delayMicroseconds(30);
    }
    delay(2);
  }
}

// ---------------- LED colores ----------------
void setColor(bool r, bool g, bool b) {
  digitalWrite(LED1, r);
  digitalWrite(LED2, g);
  digitalWrite(LED3, b);
}

void blinkColor(const char* name, bool r, bool g, bool b) {
  Serial.print("Blinking ");
  Serial.println(name);

  for (int i = 0; i < 3; i++) {
    setColor(r, g, b);
    delay(300);
    setColor(0, 0, 0);
    delay(300);
  }
}

// ---------------- BUZZER ON/OFF ----------------
void beep(int onTime, int offTime, int times) {
  for (int i = 0; i < times; i++) {
    digitalWrite(BUZZER, HIGH);
    delay(onTime);
    digitalWrite(BUZZER, LOW);
    delay(offTime);
  }
}

// ---------------- BUZZER PWM (software) ----------------
void playTone(int freq, int duration_ms) {
  int period_us = 1000000 / freq;
  int half_period = period_us / 2;

  long cycles = (long)freq * duration_ms / 1000;

  for (long i = 0; i < cycles; i++) {
    digitalWrite(BUZZER, HIGH);
    delayMicroseconds(half_period);
    digitalWrite(BUZZER, LOW);
    delayMicroseconds(half_period);
  }
}

void buzzerPWMTest() {
  Serial.println("Starting PWM buzzer test...");

  Serial.println("Low tone (500 Hz)");
  playTone(500, 1000);

  delay(300);

  Serial.println("Mid tone (1000 Hz)");
  playTone(1000, 1000);

  delay(300);

  Serial.println("High tone (2000 Hz)");
  playTone(2000, 1000);

  delay(300);

  Serial.println("Sweep test...");
  for (int f = 500; f <= 2000; f += 100) {
    playTone(f, 100);
  }

  delay(1000);
}

// ---------------- LOOP ----------------
void loop() {

  Serial.println("Starting test LED 1...");
  pwmFade(LED1);

  Serial.println("Starting test LED 2...");
  pwmFade(LED2);

  Serial.println("Starting test LED 3...");
  pwmFade(LED3);

  // Colores
  Serial.println("Starting color blink test...");
  blinkColor("Orange", 1, 1, 0);
  blinkColor("Magenta", 1, 0, 1);
  blinkColor("Cyan", 0, 1, 1);

  // Buzzer simple
  Serial.println("Starting buzzer ON/OFF test...");
  beep(100, 100, 5);

  delay(500);

  beep(300, 300, 3);

  delay(500);

  beep(50, 50, 10);

  // Buzzer PWM (frecuencia)
  buzzerPWMTest();

  delay(2000);
}
